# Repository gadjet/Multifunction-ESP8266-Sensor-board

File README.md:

# Multifunction-ESP8266-Sensor-board
AKA Wireless window/door sensor version 4

This is another in the series of wireless Window/Door sensor boards I've been designing, yes I know I've already published version 5 but this is the design before that one, I considered it a bit of a failure really because I was aiming for lower power consumption than version 3 but because I misread the LDO's specification I ended up using more power, around 85uA against the 20uA for version 3.

This board is different to version 3 because as well as being able to be triggered with a reed switch it also has the ability to have a button added to trigger the transmission instead or as well as the reed switch (doorbell?) also there is the mounting position to add an I2C sensor board such as the BME280 or AHT10 or even an OLED display or both.

The other key difference is the ability to power the ESP8266 from a Li-Ion cell (4.2v) via the LDO or directly from a 3V source such as a couple of AA cells, this bypasses the LDO completely.

There are also a couple of jumpers on the PCB for configuring the ADC input: -
 - JP1 is open circuit by default and when shorted out it modifies the voltage divider to increase the max ADC voltage to 14V, the LDO is capable of 16V input.
 - JP2 is short circuit by default and when open circuited it disconnects the ADC input from the voltage divider, used to monitor supply voltage, allowing the internal VCCread() function to be used in the code when powering the circuit directly from the 3V input.

Improvements that can be made
Use the previous LDO (HT7333) which uses less quiescent current
Power the Sensor board from a pin of the ESP so it's only powered up when used

              *********  PLEASE NOTE  *********

Some I2C boards do not have the same pinout so please check your I2C board has the same pinout as the PCB before using it.

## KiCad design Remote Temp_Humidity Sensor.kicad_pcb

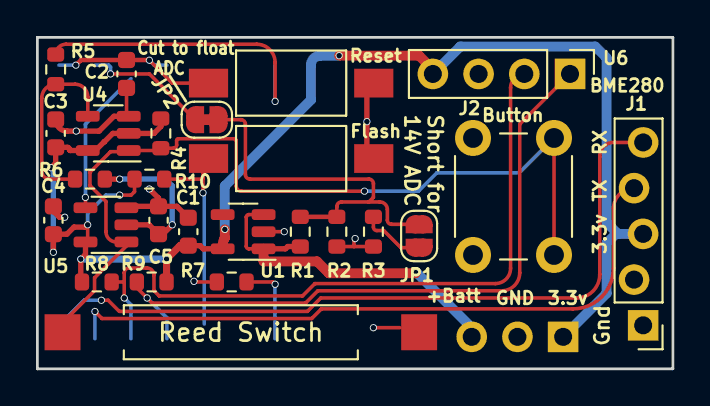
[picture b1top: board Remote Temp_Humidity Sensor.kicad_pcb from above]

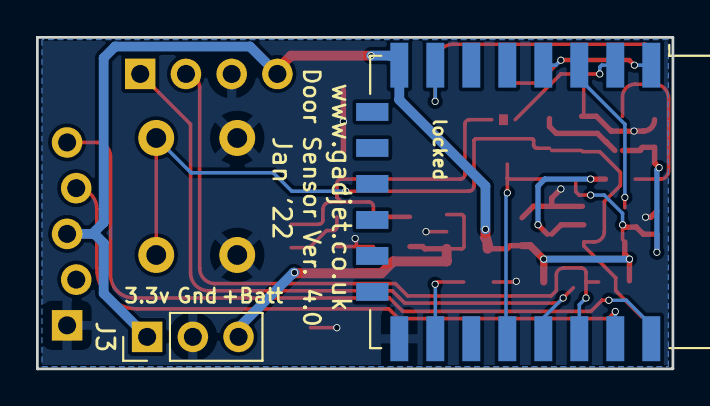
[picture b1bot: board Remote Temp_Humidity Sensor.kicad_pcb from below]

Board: 2 copper layers, 35.3 x 18.4 mm, 28 parts (2 on the bottom side), 18 nets.

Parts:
C1: 2.2uF; C_0603_1608Metric
C2, C3, C4: 100nF; C_0603_1608Metric
C5: 1uF; C_0603_1608Metric
Flash: SW_Flash; SW_SPST_FSMSM
J1: Conn_01x05_Male; PinHeader_1x05_P2.54mm_Vertical
J2: Conn_01x02_Male; SW_PUSH_6mm_H7.3mm
J3: Conn_01x03; PinHeader_1x03_P2.54mm_Vertical
JP1: Jumper_2_Open; SolderJumper-2_P1.3mm_Open_RoundedPad1.0x1.5mm
JP2: SolderJumper_2_Bridged; SolderJumper-2_P1.3mm_Bridged_RoundedPad1.0x1.5mm
R1: 3M3; R_0603_1608Metric
R2, R4: 1M05; R_0603_1608Metric
R3: 330k; R_0603_1608Metric
R5, R6, R7, R10: 10K; R_0603_1608Metric
R8, R9: 4K7; R_0603_1608Metric
Reed Switch: SW_Reed; SW_SPST_REED_CT10-XXXX-G2
Reset: SW_Reset; SW_SPST_FSMSM
U1: SPX3819M5-L-3-3; SOT-23-5
U4, U5: 74AHC1G86; SOT-23-5
U6: AHT10; PinHeader_1x04_P2.54mm_Vertical
locked: ESP-12F; ESP-12E

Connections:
+BATT: J3.3, R1.1, U1.1 (IN), U1.3 (EN)
EN: U5.4, locked.3 (EN)
GND: C1.2, C2.2, C3.2, C4.2, C5.2, Flash.2, J1.1, J2.2, J3.2, R2.2, R3.2, R7.2, Reed Switch.1, Reset.1, U1.2 (GND), U4.3 (GND), U5.3 (GND), U6.3 (Gnd), locked.15 (GND)
GPIO13: R5.2, locked.7 (GPIO13)
unnamed: C5.1, R6.2, U5.2
unnamed: J1.4, locked.21 (GPIO3/RXD)
unnamed: J1.5, locked.22 (GPIO1/TXD)
unnamed: J2.1, R4.2, Reed Switch.2, U4.1, U5.1
unnamed: JP1.1 (A), R3.1
unnamed: JP1.2 (B), JP2.1 (A), R1.2, R2.1
unnamed: JP2.2 (B), locked.2 (ADC)
unnamed: R5.1, R6.1, U4.4
unnamed: R7.1, locked.16 (GPIO15)
unnamed: Flash.1, R10.2, locked.18 (GPIO0)
unnamed: C2.1, Reset.2, locked.1 (~RST), locked.4 (GPIO16)
SCL: R8.2, U6.2 (SCL), locked.20 (GPIO5)
SDA: R9.2, U6.1 (SDA), locked.19 (GPIO4)
VCC: C1.1, C3.1, C4.1, J1.3, J3.1, R4.1, R8.1, R9.1, R10.1, U1.5 (OUT), U4.2, U4.5 (VCC), U5.5 (VCC), U6.4 (VCC), locked.8 (VCC)

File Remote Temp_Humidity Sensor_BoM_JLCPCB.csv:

Comment,Designator,Footprint,LCSC part number
2.2uF,C1,Capacitor_SMD:C_0603_1608Metric,C71000
100nF,"C2, C3, C4",Capacitor_SMD:C_0603_1608Metric,C14663
1uF,C5,Capacitor_SMD:C_0603_1608Metric,C15849
3M3,R1,Resistor_SMD:R_0603_1608Metric,C39227
1M05,"R2, R4",Resistor_SMD:R_0603_1608Metric,C247058
330k,R3,Resistor_SMD:R_0603_1608Metric,C23137
10K,"R5, R6, R7, R10",Resistor_SMD:R_0603_1608Metric,C25804
4K7,"R8, R9",Resistor_SMD:R_0603_1608Metric,C705902
SPX3819M5-L-3-3,U1,Package_TO_SOT_SMD:SOT-23-5,C9055
74AHC1G86,"U4, U5",Package_TO_SOT_SMD:SOT-23-5,C460494

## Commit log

2022-04-20 Update README.md
    First try.
2022-04-20 Add files via upload
    Images of the PCB
2022-04-20 Add files via upload
    Sketch to send Temp and Humidity data every 15 Min's using ESP-NOW
2022-04-20 Add files via upload
    PDF of the Schematic diagram
2022-04-20 Add files via upload
    KiCAD PCB layout
2022-04-20 Add files via upload
    KiCAD files
2022-04-20 Add files via upload
    Production Gerber files
2022-04-20 Add files via upload
    JLCPCB BOM file
2022-04-20 Add files via upload
    JLCPCB Component position files
2022-04-20 Update README.md
    Added some text to clarify a point
2022-04-20 Update README.md
    Added Improvements details and I2C connection warning
